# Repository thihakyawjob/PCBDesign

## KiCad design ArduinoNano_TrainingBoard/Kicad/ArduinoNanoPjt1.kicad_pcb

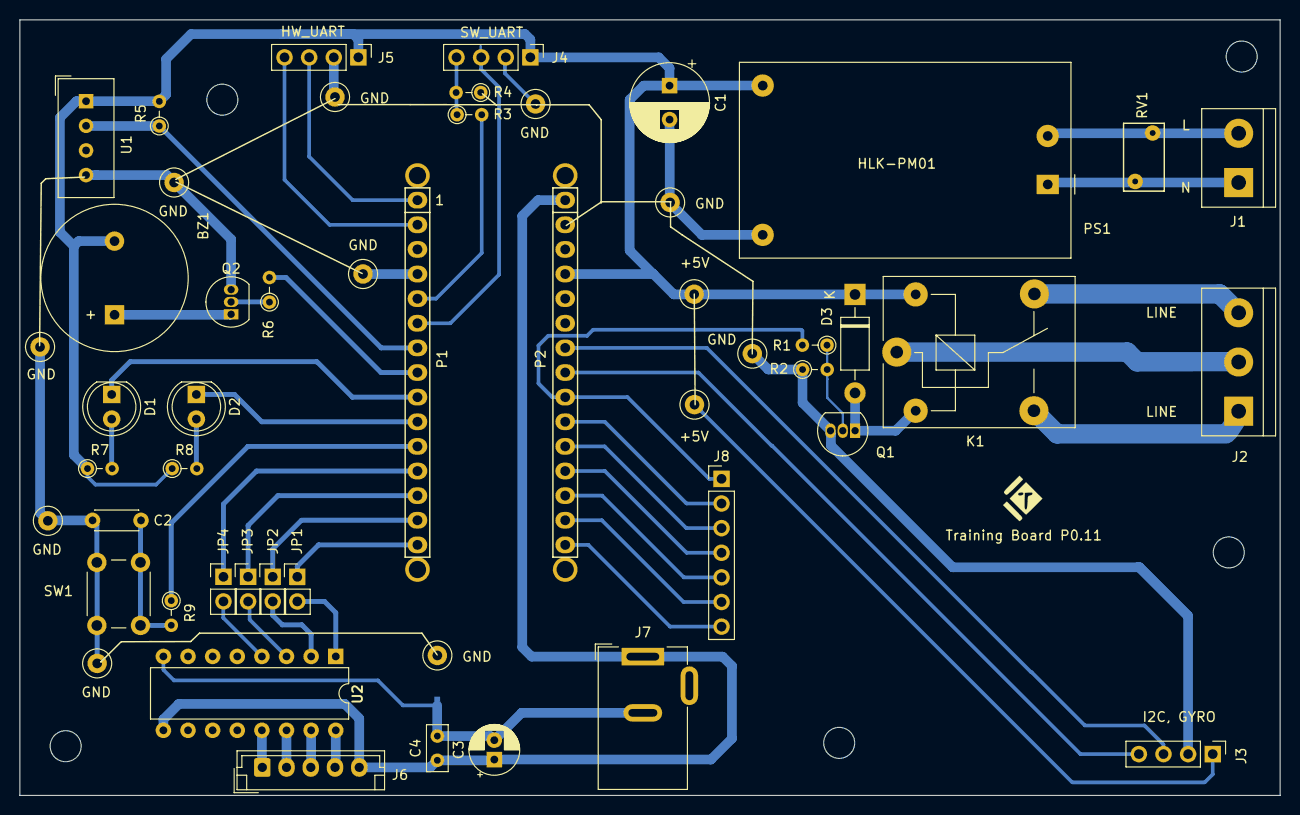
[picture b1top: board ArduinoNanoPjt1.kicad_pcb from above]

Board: 2 copper layers, 130.0 x 80.0 mm, 56 parts (1 on the bottom side), 48 nets.

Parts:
+5V, +5V#2: TestPoint_Loop_D1.80mm_Drill1.0mm_Beaded
BZ1: Buzzer; Buzzer_15x7.5RM7.6
C1: 10uF; CP_Radial_D8.0mm_P3.50mm
C2: 1uF; C_Disc_D4.3mm_W1.9mm_P5.00mm
C3: 100uF; CP_Radial_D5.0mm_P2.00mm
C4: 100nF; C_Rect_L4.6mm_W2.0mm_P2.50mm_MKS02_FKP02
D1, D2: LED; LED_D5.0mm
D3: 1N5819; D_DO-41_SOD81_P10.16mm_Horizontal
GND: TestPoint_Loop_D1.80mm_Drill1.0mm_Beaded
GND#2, GND#3, GND#4, GND#5, GND#6, GND#7, GND#8, GND#9, GND#10: TestPoint_Loop_D1.80mm_Drill1.0mm_Beaded
J1: Screw_Terminal_01x02; TerminalBlock_bornier-2_P5.08mm
J2: Screw_Terminal_01x03; TerminalBlock_bornier-3_P5.08mm
J3: I2C; PinHeader_1x04_P2.54mm_Vertical
J4, J5: SW-UART; PinHeader_1x04_P2.54mm_Vertical
J6: Conn_01x05_Male; JST_EH_B5B-EH-A_1x05_P2.50mm_Vertical
J7: Jack-DC; BarrelJack_Wuerth_6941xx301002
J8: Conn_01x07; PinHeader_1x07_P2.54mm_Vertical
JP1, JP2, JP3, JP4: Jumper; PinHeader_1x02_P2.54mm_Vertical
K1: SANYOU_SRD_Form_C; Relay_SPDT_SANYOU_SRD_Series_Form_C
L1: L_Core_Ferrite; SolderJumper-2_P1.3mm_Bridged_RoundedPad1.0x1.5mm
P1: Digital; Socket_Strip_Arduino_1x15
P2: Analog; Socket_Strip_Arduino_1x15
P3, P4, P5, P6: CONN_01X01; 1pin_Nano
PS1: HLK-PM01; Converter_ACDC_HiLink_HLK-PMxx
Q1, Q2: BC547; TO-92_Inline
R1, R6, R7, R8: 2K2; R_Axial_DIN0204_L3.6mm_D1.6mm_P2.54mm_Vertical
R2: 47K; R_Axial_DIN0204_L3.6mm_D1.6mm_P2.54mm_Vertical
R3: 2K; R_Axial_DIN0204_L3.6mm_D1.6mm_P2.54mm_Vertical
R4: 4.6K; R_Axial_DIN0204_L3.6mm_D1.6mm_P2.54mm_Vertical
R5: 10K; R_Axial_DIN0204_L3.6mm_D1.6mm_P2.54mm_Vertical
R9: 100; R_Axial_DIN0204_L3.6mm_D1.6mm_P2.54mm_Vertical
RV1: Varistor; RV_Disc_D7mm_W4.2mm_P5mm
SW1: SW_DIP_x01; SW_PUSH_6mm
U1: DHT11; Aosong_DHT11_5.5x12.0_P2.54mm
U2: ULN2003A; DIP-16_W7.62mm

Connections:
+3V3: J8.6, P2.14
+5V: +5V.1, +5V#2.1, BZ1.2, C1.1, D3.1, J3.1, J4.1, J5.1, K1.5, P2.4, PS1.4, R5.2, R7.1, R8.1, U1.1
+12V: C3.1, C4.1, J6.5, J7.1, P2.1, U2.9
/13(SCK): J8.7, P2.15
/A0: J8.4, P2.12
/A1: J8.3, P2.11
/A2: J8.2, P2.10
/A3: J8.1, P2.9, R1.2
/A4: J3.4, P2.8
/A5: J3.3, P2.7
/AREF: J8.5, P2.13
/D4: P1.7, R5.1, U1.2
/D5: P1.8, R6.2
/D6: D1.1, P1.9
/D7: D2.1, P1.10
/D8: P1.11, R9.1
/D9: JP4.1, P1.12
/D10_SS: JP3.1, P1.13
/D11_MOSI: JP2.1, P1.14
/D12_MISO: JP1.1, P1.15
/RXD: J5.4, P1.2
/Reset: P1.3, P2.3
/SW_RXD: P1.5, R3.2
/SW_TXD: J4.3, P1.6
/TXD: J5.3, P1.1
GND: C1.2, C2.2, GND.1, GND#2.1, GND#3.1, GND#4.1, GND#5.1, GND#6.1, GND#7.1, GND#8.1, GND#9.1, GND#10.1, J3.2, J4.2, J5.2, L1.2, P1.4, P2.2, PS1.3, Q1.3, Q2.3, R2.1, R4.1, SW1.1, U1.4
GNDA: C3.2, C4.2, J7.2, L1.1, U2.8
unnamed: BZ1.1, Q2.1
unnamed: C2.1, R9.2, SW1.2
unnamed: D1.2, R7.2
unnamed: D2.2, R8.2
unnamed: D3.2, K1.2, Q1.1
unnamed: J1.1, PS1.1, RV1.1
unnamed: J1.2, PS1.2, RV1.2
unnamed: J2.1, K1.3
unnamed: J2.2, K1.1
unnamed: J2.3, K1.4
unnamed: J4.4, R3.1, R4.2
unnamed: J6.1, U2.13
unnamed: J6.2, U2.14
unnamed: J6.3, U2.15
unnamed: J6.4, U2.16
unnamed: JP1.2, U2.1
unnamed: JP2.2, U2.2
unnamed: JP3.2, U2.3
unnamed: JP4.2, U2.4
unnamed: Q1.2, R1.1, R2.2
unnamed: Q2.2, R6.1

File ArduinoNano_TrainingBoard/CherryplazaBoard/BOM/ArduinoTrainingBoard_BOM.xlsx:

Item | Qty | Reference(s) | Value | Description
1 | 1 | BZ1 | Buzzer | Piezo NO 4000Hz 85dB @ 5V, 10cm 5V Φ14mm Through Hole,P=7.6mm Buzzers RoHS
2 | 1 | C1 | 10uF | 10uF ±20% 250V 8x14 Radial,8x14mm Aluminum Electrolytic Capacitors - Leaded RoH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
3 | 1 | C2 | 1uF | 1uF ±10% 50V Through Hole,P=5.08mm Ceramic Disc Capacitors RoHS
4 | 1 | C3 | 100uF | 100uF ±20% 50V 8x12 2000Hrs @ 105℃ Radial,8x12mm Aluminum Electrolytic Capacito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
5 | 1 | C4 | 100nF | 100nF -20%~+80% 25V Through Hole,P=2.54mm Ceramic Disc Capacitors RoHS
6 | 2 | C5, C6 | 1uF | 1uF ±20% 50V 4x5 1000Hrs @ 105℃ Radial,4x5mm Aluminum Electrolytic Capacitors -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
7 | 2 | D1, D2 | LED | Device:LED
8 | 1 | D3 | 1N5819 | Diode:1N5819
9 | 1 | J3 | I2C | Connector_Generic:Conn_01x04
10 | 2 | J4, J5 | SW-UART | Connector_Generic:Conn_01x04
11 | 1 | J6 | Conn_01x05_Male | Connector:Conn_01x05_Male
12 | 1 | J7 | Jack-DC | Connector:Jack-DC
13 | 1 | K1 | SANYOU_SRD_Form_C | Relay:SANYOU_SRD_Form_C
14 | 1 | P1 | Digital | Female Header Female Socket 0.100"(2.54mm) 15 1 Through Hole,P=2.54mm Pin Heade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
15 | 1 | P2 | Analog | Female Header Female Socket 0.100"(2.54mm) 15 1 Through Hole,P=2.54mm Pin Heade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
16 | 2 | Q1, Q2 | BC547 | Transistor_BJT:BC547
17 | 4 | R1, R6, R7, R8 | 2K2 | Device:R
18 | 1 | R2 | 47K | Device:R
19 | 1 | R3 | 2K | Device:R
20 | 1 | R4 | 4.7K | Device:R
21 | 1 | R5 | 10K | Device:R
22 | 1 | R9 | 100 | Device:R
23 | 1 | SW1 | SW_DIP_x01 | Switch:SW_DIP_x01
24 | 1 | U1 | DHT11 | Sensor:DHT11
25 | 1 | U2 | ULN2003A | Transistor_Array:ULN2003A

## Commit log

2020-05-01 Add UART Isolation PCB File
    Sch
    Gerber
2020-05-07 Upload ArduinoNano TrainingBoard Gerber File added
2020-05-08 Update PCB
    Add Diode
    Add Mounting Hole
2020-05-08 File reorginise
2020-06-19 Upload CherryPlazaBoard
2020-06-20 Add Arduino Example Codes
2020-06-20 Update Relay code
2020-06-20 Add 4 Digit Clock Display
2020-07-05 Arduino Nano Shield example code uploaded
2020-07-05 Uploaded Arduino
2020-07-25 Add more codes
2021-06-30 Add Kicad Library
